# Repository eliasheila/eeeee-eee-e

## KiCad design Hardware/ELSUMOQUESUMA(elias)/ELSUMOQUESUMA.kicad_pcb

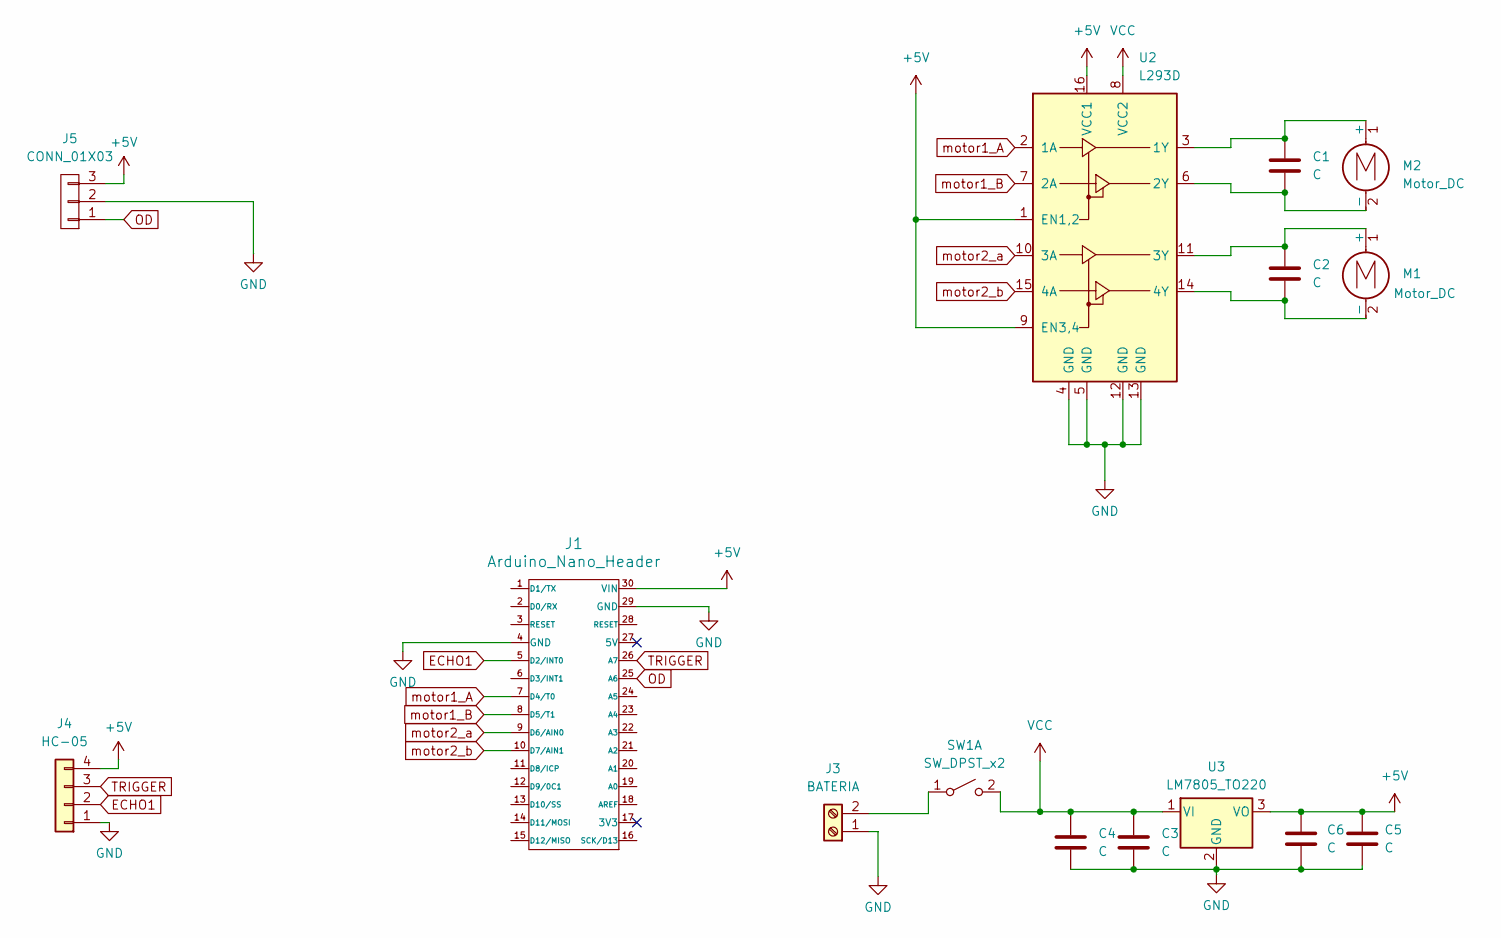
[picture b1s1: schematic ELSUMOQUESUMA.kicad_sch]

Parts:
C1, C2, C4, C5: C; C_0805
C3, C6: C; CP_Radial_D5.0mm_P2.50mm
J1: Arduino_Nano_Header; arduino_nano_header
J3: BATERIA; BORNERA2_AZUL
J4: HC-05; pin_strip_4
J5: CONN_01X03; PinHeader_1x03_P2.54mm_Vertical
M1, M2: Motor_DC; BORNERA2_AZUL
SW1: SW_DPST_x2; Pin_strip_2
U2: L293D; DIP_16-300_socket
U3: LM7805_TO220; TO-263-3_TabPin2

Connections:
+5V: C5.2, C6.2, J1.30 (VIN), J4.4, J5.3, U2.1 (EN1,2), U2.9 (EN3,4), U2.16 (VCC1), U3.3 (VO)
ECHO1: J1.5 (D2/INT0), J4.2
GND: C3.1, C4.1, C5.1, C6.1, J1.4 (GND), J1.29 (GND), J3.1, J4.1, J5.2, U2.4 (GND), U2.5 (GND), U2.12 (GND), U2.13 (GND), U3.2 (GND)
unnamed: J3.2, SW1.1 (A)
unnamed: C2.1, M1.1 (+), U2.11 (3Y)
unnamed: C2.2, M1.2 (-), U2.14 (4Y)
unnamed: C1.1, M2.1 (+), U2.3 (1Y)
unnamed: C1.2, M2.2 (-), U2.6 (2Y)
OD: J1.25 (A6), J5.1
TRIGGER: J1.26 (A7), J4.3
VCC: C3.2, C4.2, SW1.2 (B), U2.8 (VCC2), U3.1 (VI)
motor1_A: J1.7 (D4/T0), U2.2 (1A)
motor1_B: J1.8 (D5/T1), U2.7 (2A)
motor2_a: J1.9 (D6/AIN0), U2.10 (3A)
motor2_b: J1.10 (D7/AIN1), U2.15 (4A)

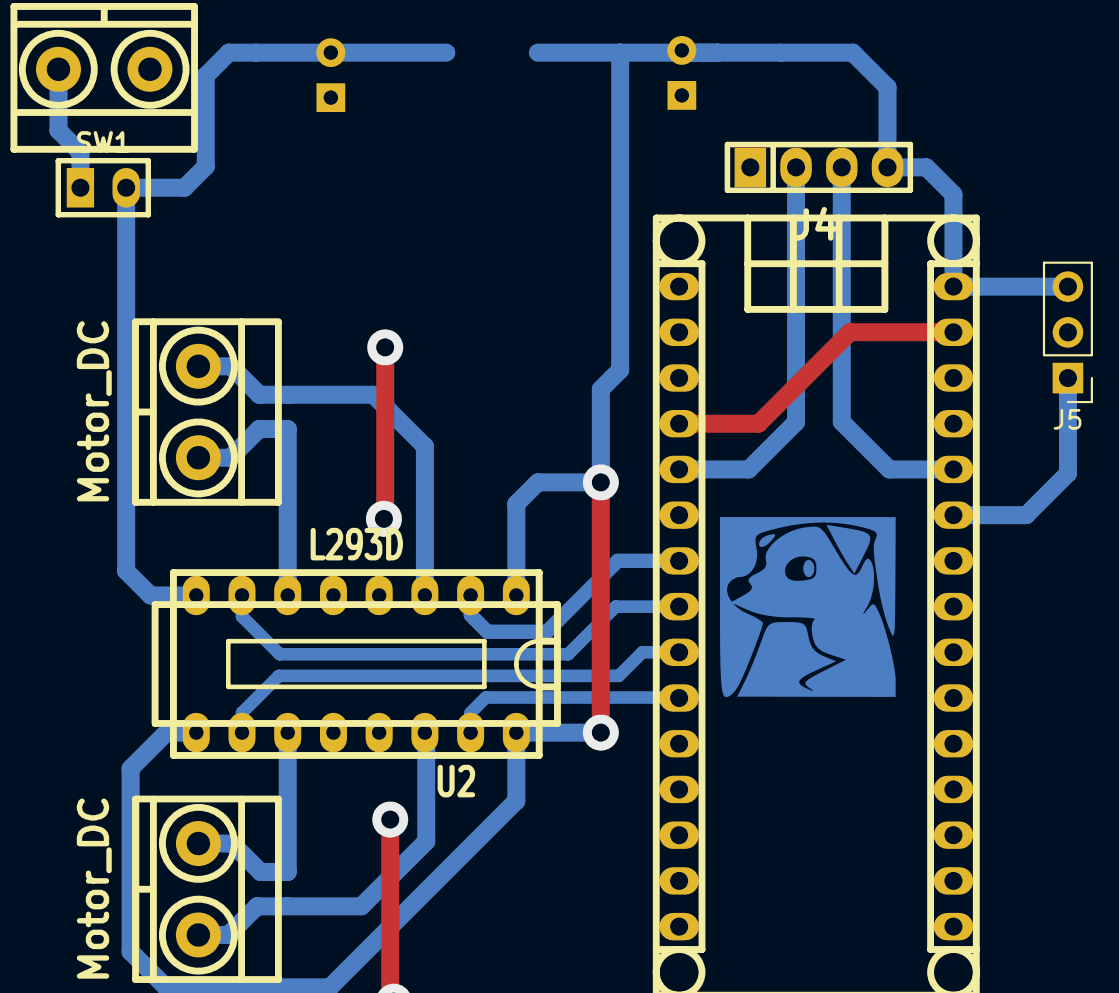
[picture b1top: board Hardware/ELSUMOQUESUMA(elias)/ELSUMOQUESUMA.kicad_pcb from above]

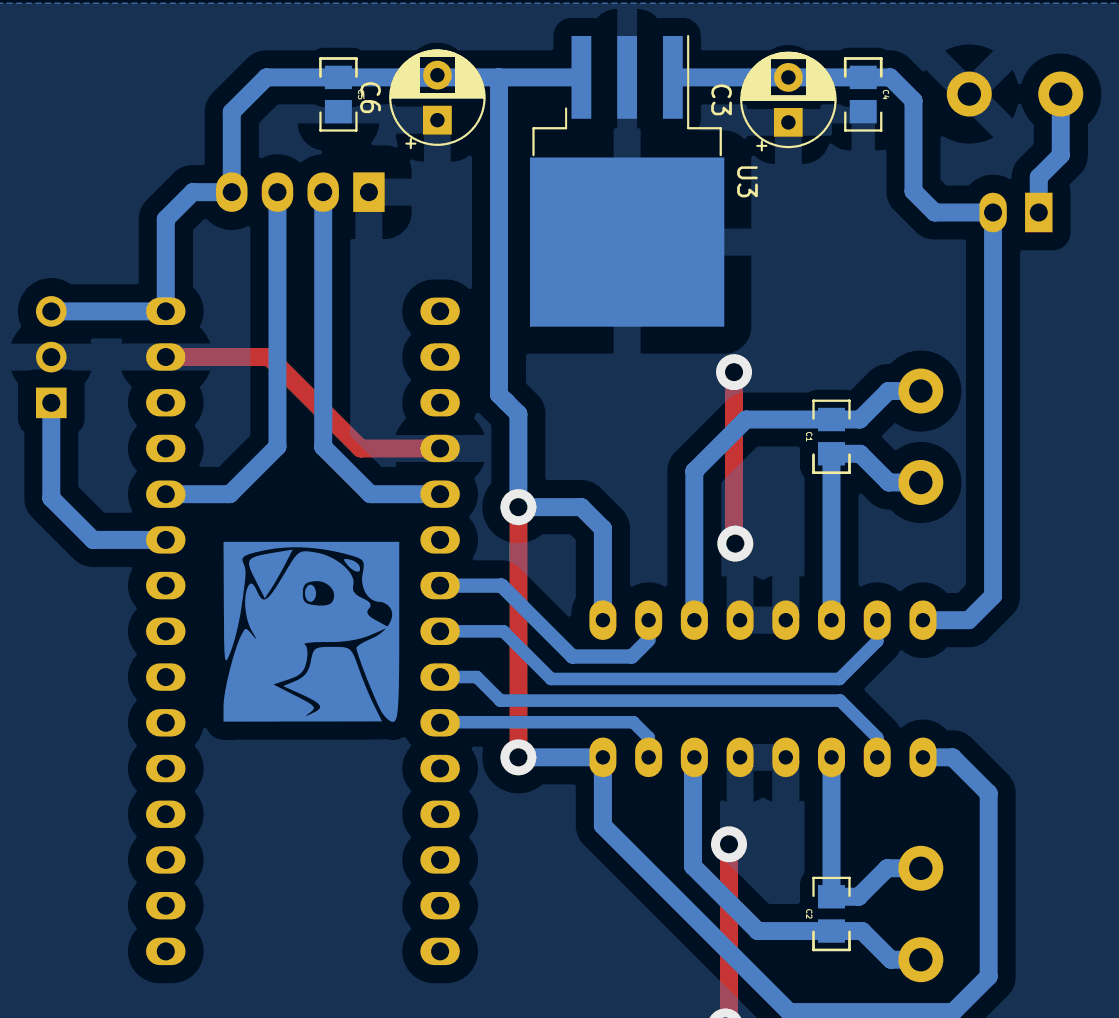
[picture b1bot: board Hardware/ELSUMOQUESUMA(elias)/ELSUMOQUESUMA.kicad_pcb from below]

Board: 2 copper layers, 15 parts (7 on the bottom side), 15 nets.

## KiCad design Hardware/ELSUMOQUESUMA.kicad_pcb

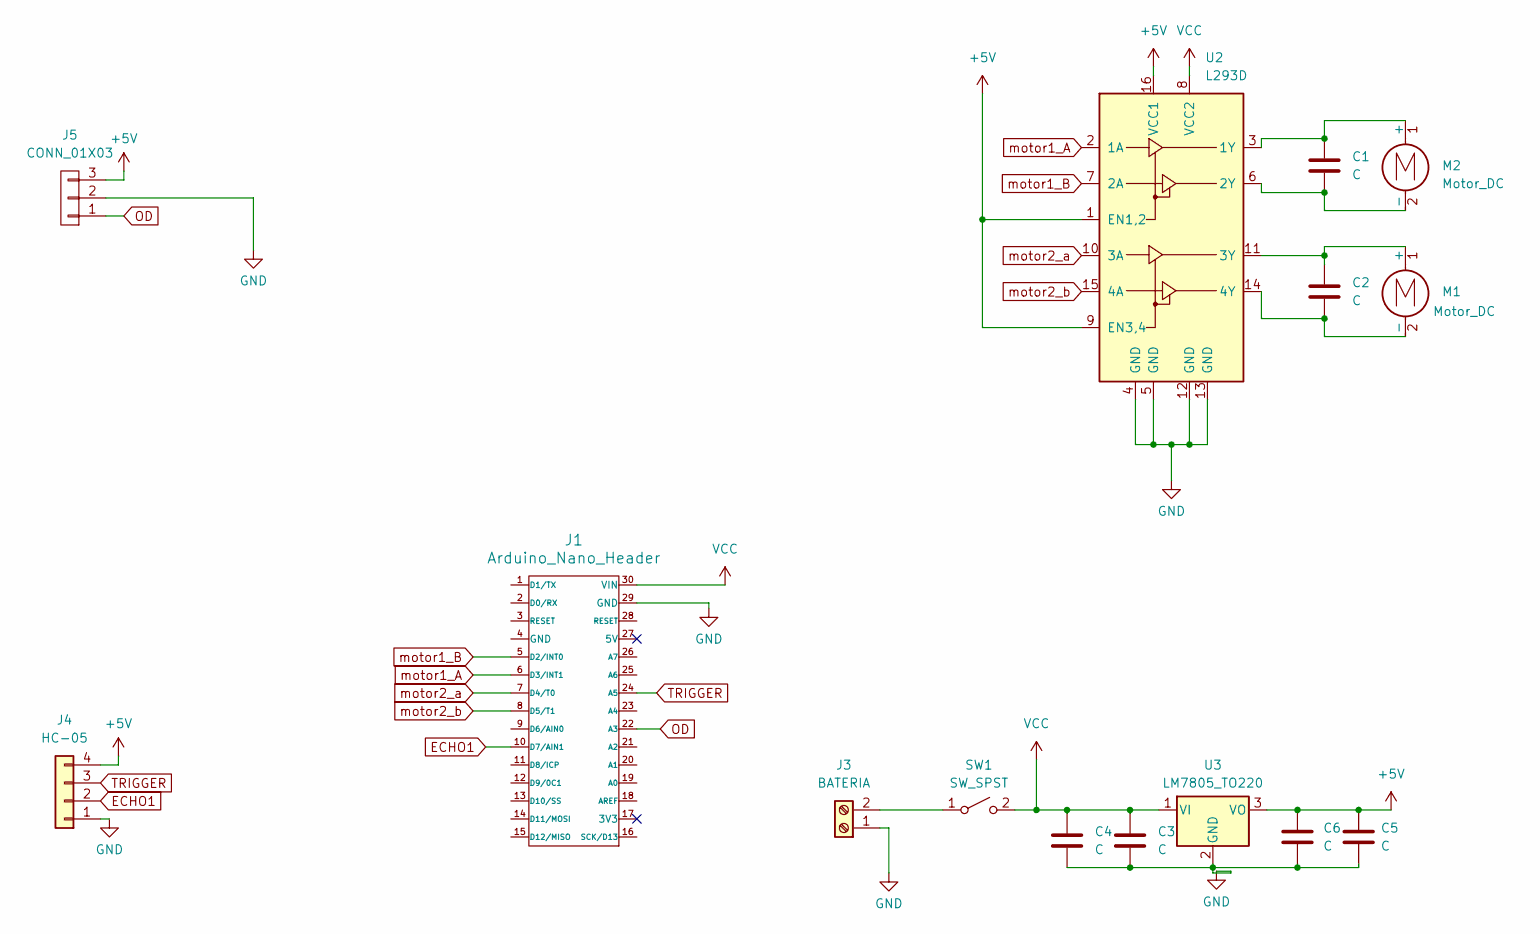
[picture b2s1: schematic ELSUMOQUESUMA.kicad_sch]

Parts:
C1, C2, C3, C6: C; C_Disc_D3.0mm_W1.6mm_P2.50mm
C4, C5: C; CAP_ELEC_5x11mm
J1: Arduino_Nano_Header; arduino_nano_header
J3: BATERIA; BORNERA2_AZUL
J4: HC-05; pin_strip_4
J5: CONN_01X03; PinHeader_1x03_P2.54mm_Vertical
M1, M2: Motor_DC; BORNERA2_AZUL
SW1: SW_SPST; Pin_Header_2
U2: L293D; DIP_16-300_socket
U3: LM7805_TO220; to220

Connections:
+5V: C5.2, C6.2, J4.4, J5.3, U2.1 (EN1,2), U2.9 (EN3,4), U2.16 (VCC1), U3.3 (VO)
ECHO1: J1.10 (D7/AIN1), J4.2
GND: C3.1, C4.1, C5.1, C6.1, J1.29 (GND), J3.1, J4.1, J5.2, U2.4 (GND), U2.5 (GND), U2.12 (GND), U2.13 (GND), U3.2 (GND)
unnamed: J3.2, SW1.1 (A)
unnamed: C2.1, M1.1 (+), U2.11 (3Y)
unnamed: C2.2, M1.2 (-), U2.14 (4Y)
unnamed: C1.1, M2.1 (+), U2.3 (1Y)
unnamed: C1.2, M2.2 (-), U2.6 (2Y)
OD: J1.22 (A3), J5.1
TRIGGER: J1.24 (A5), J4.3
VCC: C3.2, C4.2, J1.30 (VIN), SW1.2 (B), U2.8 (VCC2), U3.1 (VI)
motor1_A: J1.6 (D3/INT1), U2.2 (1A)
motor1_B: J1.5 (D2/INT0), U2.7 (2A)
motor2_a: J1.7 (D4/T0), U2.10 (3A)
motor2_b: J1.8 (D5/T1), U2.15 (4A)

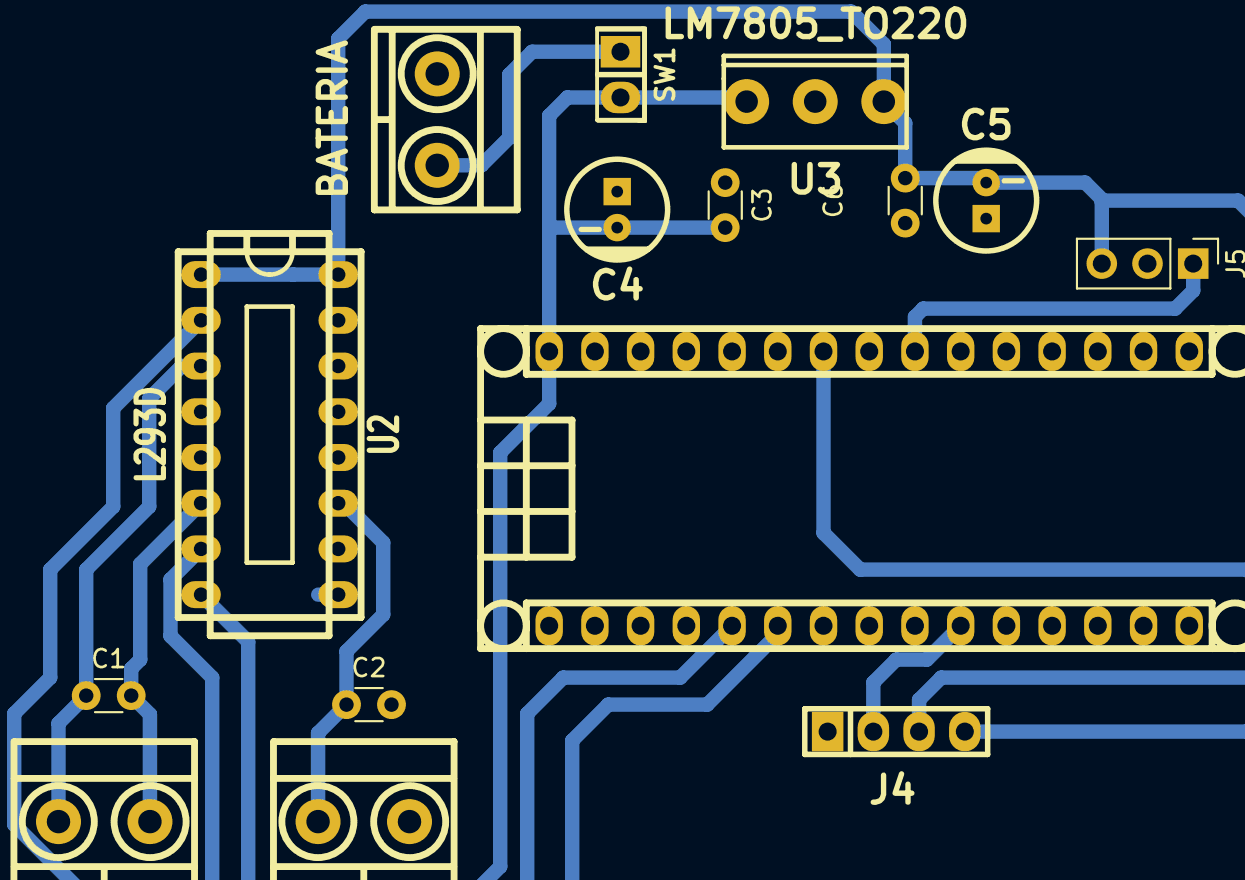
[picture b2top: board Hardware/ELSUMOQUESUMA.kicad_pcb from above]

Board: 2 copper layers, 15 parts (0 on the bottom side), 15 nets.

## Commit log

2026-03-17 Mi primer commit
2026-03-17 Modificamos titulo en index.html
2026-03-17 Se agregaron carpetas para el proyecto
2026-05-18 basura
2026-05-18 bsur
